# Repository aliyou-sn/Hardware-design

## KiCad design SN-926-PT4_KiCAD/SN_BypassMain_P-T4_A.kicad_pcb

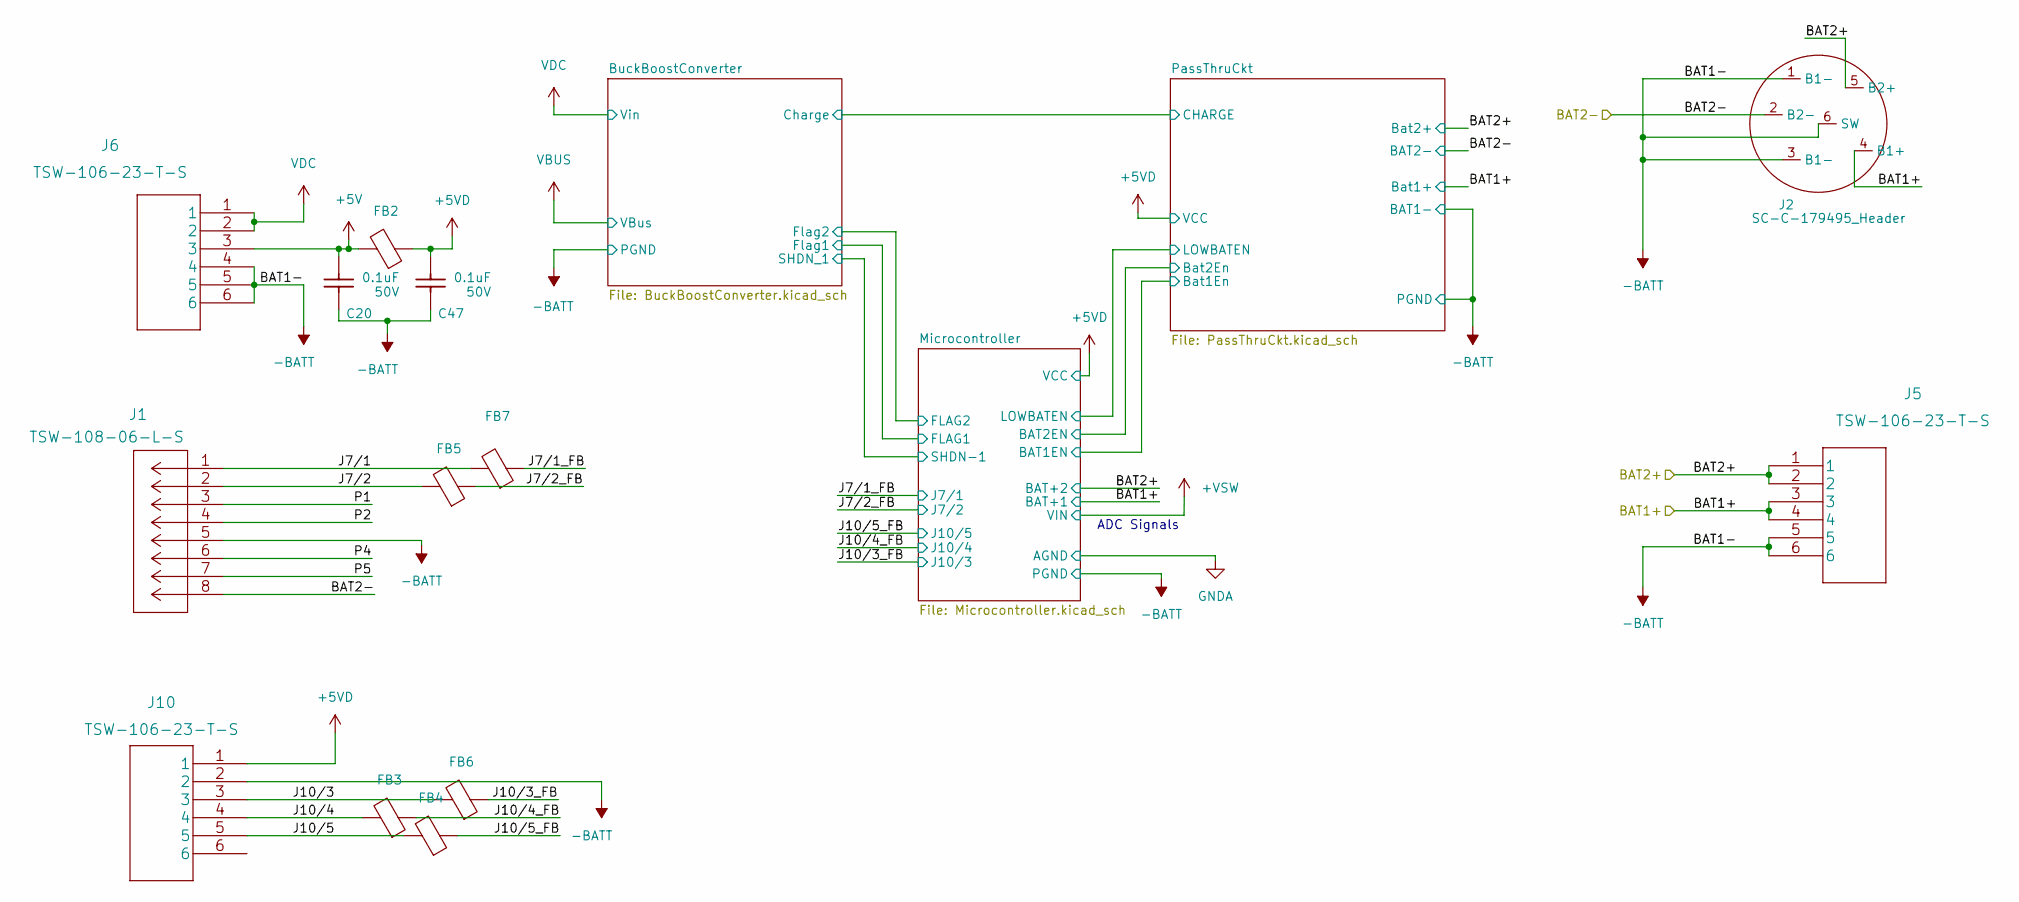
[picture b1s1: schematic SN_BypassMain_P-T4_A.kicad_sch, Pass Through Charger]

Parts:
C20, C47: 0.1uF; C_0603_1608Metric; VOLTAGE 50V; TOLERANCE +/-5%; MANUFACTURER PARTNO 2 12062C104JAT2A
FB2, FB3, FB4, FB5, FB6, FB7: BLM21AG121BH1D; L_0805_2012Metric
J1: TSW-108-06-L-S
J2: SC-C-179495_Header; SC-C-179495_HEADER
J5, J6, J10: TSW-106-23-T-S

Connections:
+5V: C20.2, FB2.2, J6.3
+5VD: C47.2, FB2.1, J10.1; also elsewhere on the board
-BATT: C20.1, C47.1, J1.5, J2.1 (B1-), J2.3 (B1-), J2.6 (SW), J5.5, J5.6, J6.4, J6.5, J6.6, J10.2; also elsewhere on the board
/BAT1+: J2.4 (B1+), J5.3, J5.4; also elsewhere on the board
/BAT2+: J2.5 (B2+), J5.1, J5.2; also elsewhere on the board
/BAT2-: J1.8, J2.2 (B2-); also elsewhere on the board
/J7/1: FB7.2, J1.1
/J7/1_FB: FB7.1; also elsewhere on the board
/J7/2: FB5.2, J1.2
/J7/2_FB: FB5.1; also elsewhere on the board
/J10/3: FB6.2, J10.3
/J10/3_FB: FB6.1; also elsewhere on the board
/J10/4: FB3.2, J10.4
/J10/4_FB: FB3.1; also elsewhere on the board
/J10/5: FB4.2, J10.5
/J10/5_FB: FB4.1; also elsewhere on the board
/P1: J1.3
/P2: J1.4
/P4: J1.6
/P5: J1.7
VDC: J6.1, J6.2; also elsewhere on the board

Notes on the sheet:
ADC Signals

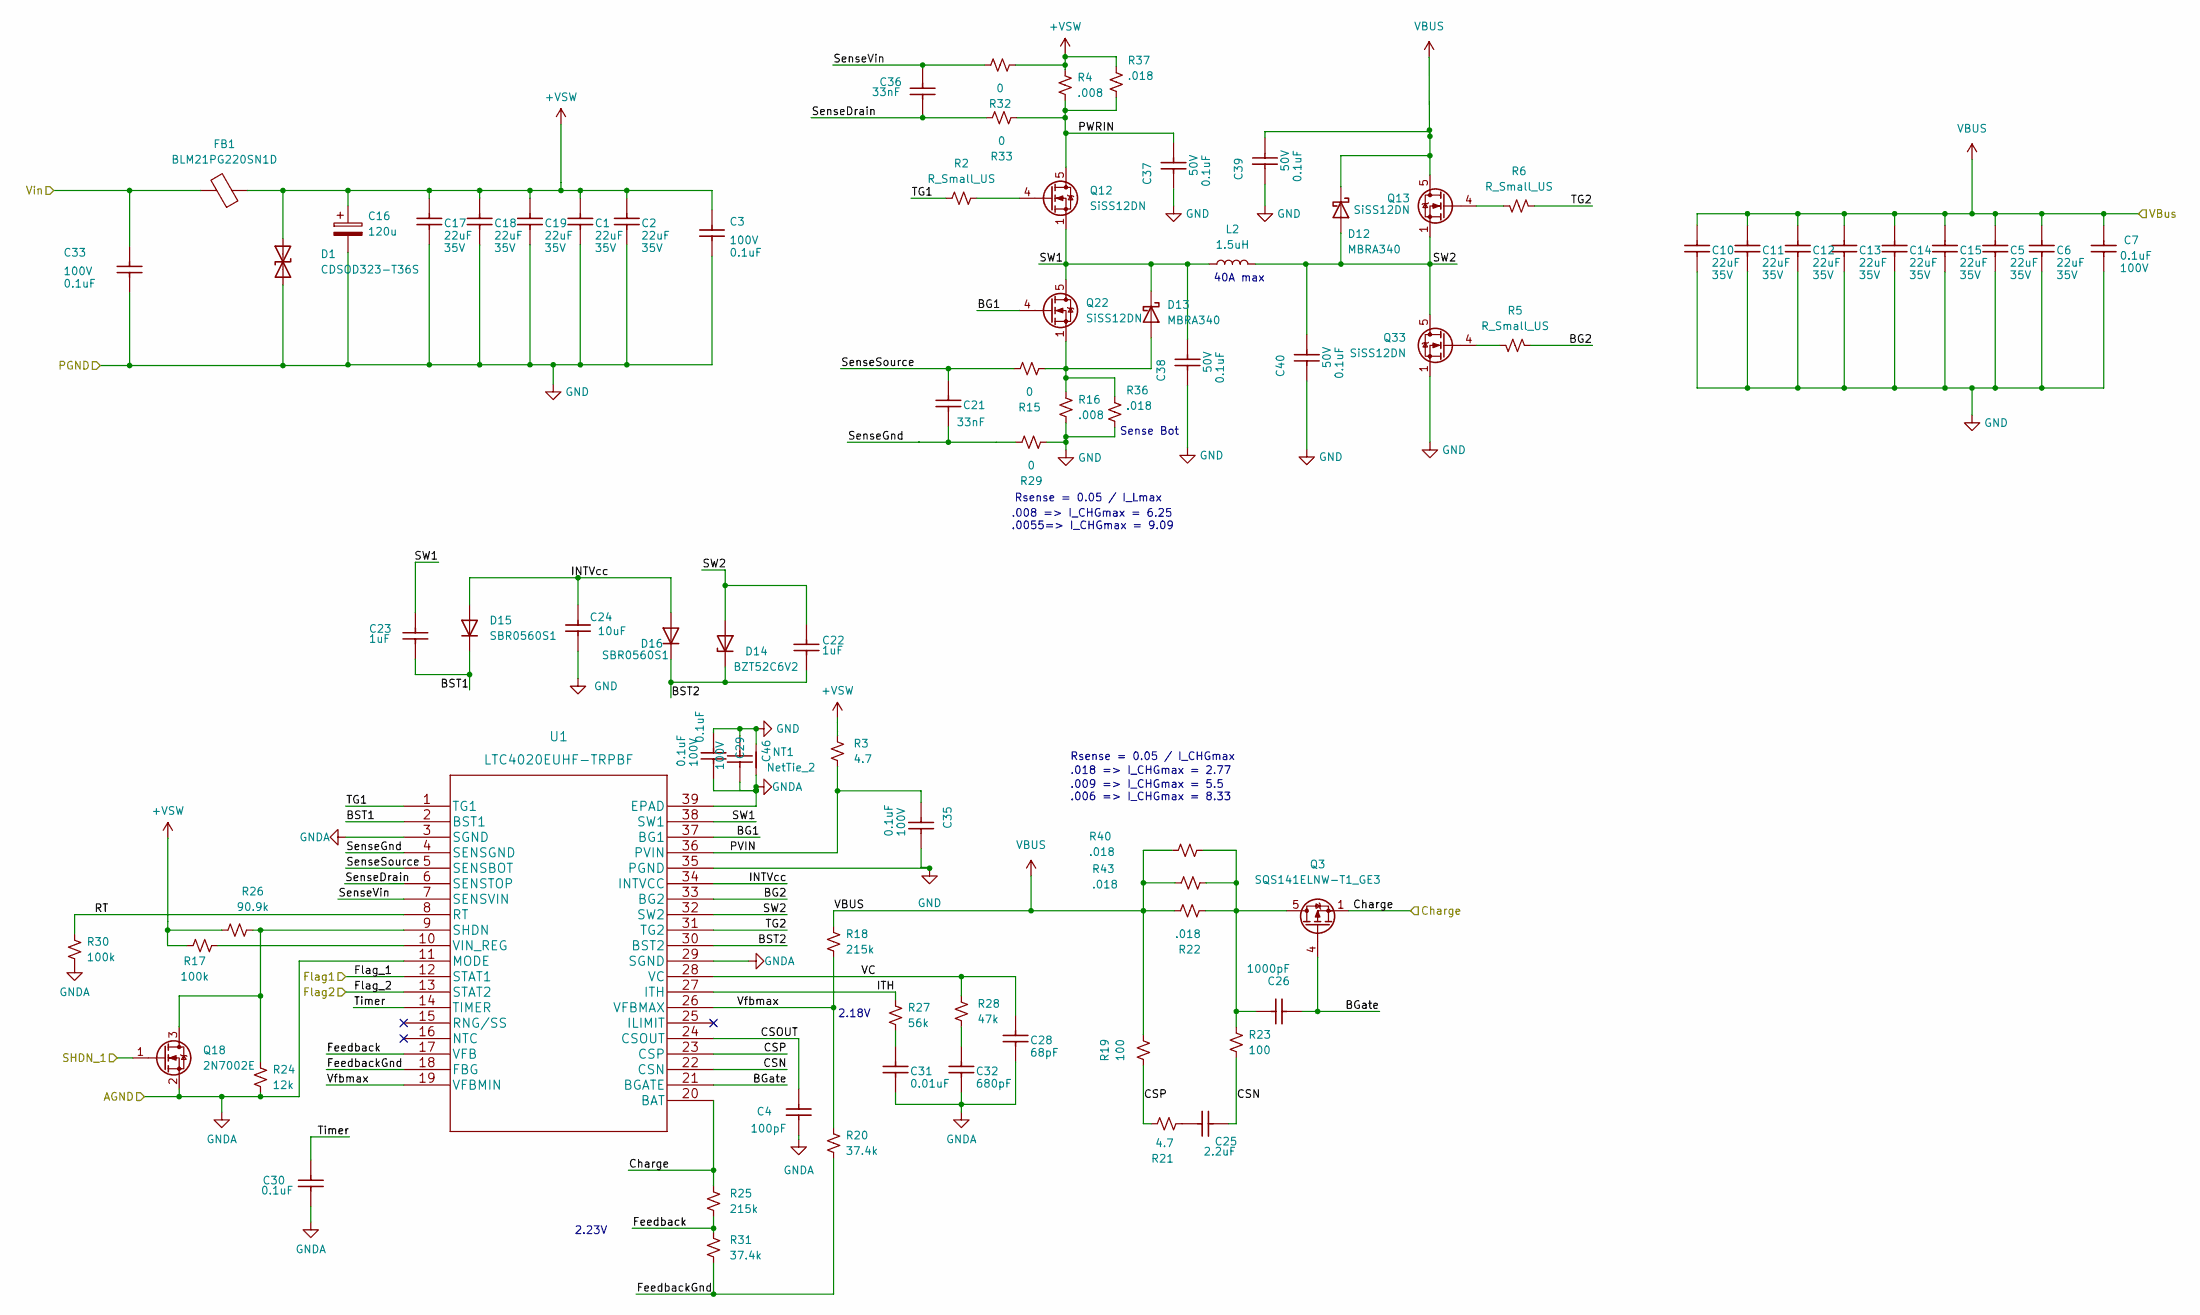
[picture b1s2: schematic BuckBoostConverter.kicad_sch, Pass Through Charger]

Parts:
C1, C2, C5, C6, C10, C11, C12, C13, C14, C15, C17, C18, C19: 22uF; C_1206_3216Metric; VOLTAGE 35V; TOLERANCE 20%; MANUFACTURER PARTNO C3216JB1V226M160AC
C3, C7, C29, C33, C35, C46: 0.1uF; C_0603_1608Metric; VOLTAGE 100V; TOLERANCE +/-5%; MANUFACTURER PARTNO 2 12062C104JAT2A
C4: 100pF; C_0402_1005Metric
C16: 120u; CP_Elec_10x10
C21, C36: 33nF; C_0402_1005Metric
C22, C23: 1uF; C_0603_1608Metric
C24: 10uF; C_1206_3216Metric
C25: 2.2uF; C_0402_1005Metric
C26: 1000pF; C_0402_1005Metric
C28: 68pF; C_0603_1608Metric
C30: 2.2uF; R_0402_1005Metric
C31: 0.01uF; C_0603_1608Metric
C32: 680pF; C_0603_1608Metric
C37, C38, C39, C40: 0.1uF; C_0603_1608Metric; VOLTAGE 50V; TOLERANCE +/-5%; MANUFACTURER PARTNO 2 12062C104JAT2A
D1: CDSOD323-T36S; D_SOD-323
D12, D13: MBRA340; D_SMA
D14: BZT52C6V2; D_SOD-123F
D15, D16: SBR0560S1; D_SOD-123
FB1: BLM21PG220SN1D; L_0805_2012Metric
L2: 1.5uH; XAL1010-152MEB
NT1: NetTie_2; NetTie-2_SMD_Pad0.5mm
Q3: SQS141ELNW-T1_GE3; Vishay_PowerPAK_1212-8_Single
Q12, Q13, Q22, Q33: SiSS12DN; Vishay_PowerPAK_1212-8_Single
Q18: 2N7002E; SOT-23
R2, R5, R6: R_Small_US; R_0402_1005Metric
R3: 4.7; R_0603_1608Metric
R4: .008
R15, R29, R32, R33: 0; C_0402_1005Metric
R16: .008; R_2512_6332Metric
R17, R30: 100k; R_0402_1005Metric
R18, R25: 215k; R_0402_1005Metric
R19, R23: 100; C_0402_1005Metric
R20, R31: 37.4k; R_0402_1005Metric
R21: 4.7; R_0402_1005Metric
R22, R36, R37, R40, R43: .018; R_2512_6332Metric
R24: 12k; R_0402_1005Metric
R26: 90.9k; R_0402_1005Metric
R27: 56k; R_0603_1608Metric
R28: 47k; R_0603_1608Metric
U1: LTC4020EUHF-TRPBF

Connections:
+VSW: C1.1, C2.1, C3.1, C16.1, C17.1, C18.1, C19.1, D1.1 (A1), FB1.1, R3.2, R4.2, R17.1, R26.1, R32.2, R37.2; also elsewhere on the board
-BATT: C1.2, C2.2, C3.2, C5.2, C6.2, C7.2, C10.2, C11.2, C12.2, C13.2, C14.2, C15.2, C16.2, C17.2, C18.2, C19.2, C24.1, C29.1, C33.2, C35.2, C37.1, C38.1, C39.1, C40.1, C46.1, D1.2 (A2), NT1.1, Q33.1 (S), Q33.2 (S), Q33.3 (S), R16.2, R29.2, R36.1, U1.35 (PGND); also elsewhere on the board
/BuckBoostConverter/BG1: Q22.4 (G), U1.37 (BG1)
/BuckBoostConverter/BG2: R5.1, U1.33 (BG2)
/BuckBoostConverter/BGate: C26.2, Q3.4 (G), U1.21 (BGATE); also elsewhere on the board
/BuckBoostConverter/BST1: C23.1, D15.1 (K), U1.2 (BST1)
/BuckBoostConverter/BST2: C22.1, D14.1 (K), D16.1 (K), U1.30 (BST2)
/BuckBoostConverter/CSN: C25.2, R23.1, U1.22 (CSN)
/BuckBoostConverter/CSOUT: C4.1, U1.24 (CSOUT)
/BuckBoostConverter/CSP: R19.2, R21.1, U1.23 (CSP)
/BuckBoostConverter/Charge: Q3.1 (S), Q3.2 (S), Q3.3 (S), R25.2, U1.20 (BAT); also elsewhere on the board
/BuckBoostConverter/Feedback: R25.1, R31.2, U1.17 (VFB)
/BuckBoostConverter/FeedbackGnd: R20.1, R31.1, U1.18 (FBG)
/BuckBoostConverter/Flag_1: U1.12 (STAT1); also elsewhere on the board
/BuckBoostConverter/Flag_2: U1.13 (STAT2); also elsewhere on the board
/BuckBoostConverter/INTVcc: C24.2, D15.2 (A), D16.2 (A), U1.34 (INTVCC)
/BuckBoostConverter/ITH: R27.2, U1.27 (ITH)
/BuckBoostConverter/PVIN: C35.1, R3.1, U1.36 (PVIN)
/BuckBoostConverter/PWRIN: C37.2, Q12.5 (D), R4.1, R33.2, R37.1
/BuckBoostConverter/RT: R30.1, U1.8 (RT)
/BuckBoostConverter/SW1: C23.2, C38.2, D13.1 (K), L2.1, Q12.1 (S), Q12.2 (S), Q12.3 (S), Q22.5 (D), U1.38 (SW1)
/BuckBoostConverter/SW2: C22.2, C40.2, D12.2 (A), D14.2 (A), L2.2, Q13.1 (S), Q13.2 (S), Q13.3 (S), Q33.5 (D), U1.32 (SW2)
/BuckBoostConverter/SenseDrain: C36.1, R33.1, U1.6 (SENSTOP)
/BuckBoostConverter/SenseGnd: C21.2, R29.1, U1.4 (SENSGND)
/BuckBoostConverter/SenseSource: C21.1, R15.1, U1.5 (SENSBOT)
/BuckBoostConverter/SenseVin: C36.2, R32.1, U1.7 (SENSVIN)
/BuckBoostConverter/TG1: R2.1, U1.1 (TG1)
/BuckBoostConverter/TG2: R6.1, U1.31 (TG2)
/BuckBoostConverter/Timer: C30.1, U1.14 (TIMER)
/BuckBoostConverter/VC: C28.1, R28.2, U1.28 (VC)
/BuckBoostConverter/Vfbmax: R18.1, R20.2, U1.19 (VFBMIN), U1.26 (VFBMAX)
/Microcontroller/SHDN-1: Q18.1 (G); also elsewhere on the board
GNDA: C4.2, C28.2, C29.2, C30.2, C31.2, C32.2, C46.2, NT1.2, Q18.2 (S), R24.2, R30.2, U1.3 (SGND), U1.11 (MODE), U1.29 (SGND), U1.39 (EPAD); also elsewhere on the board
unnamed: C25.1, R21.2
unnamed 59: C26.1, Q3.5 (D), Q3.6 (D), Q3.7 (D), Q3.8 (D), Q3.9 (D), R22.1, R23.2, R40.2, R43.2; also elsewhere on the board
unnamed: C31.1, R27.1
unnamed: C32.1, R28.1
unnamed: D13.2 (A), Q22.1 (S), Q22.2 (S), Q22.3 (S), R15.2, R16.1, R36.2
unnamed: Q12.4 (G), R2.2
unnamed: Q13.4 (G), R6.2
unnamed: Q18.3 (D), R24.1, R26.2, U1.9 (SHDN)
unnamed: Q33.4 (G), R5.2
unnamed: R17.2, U1.10 (VIN_REG)
VBUS: C5.1, C6.1, C7.1, C10.1, C11.1, C12.1, C13.1, C14.1, C15.1, C39.2, D12.1 (K), Q13.5 (D), R18.2, R19.1, R22.2, R40.1, R43.1
VDC: C33.1, FB1.2; also elsewhere on the board

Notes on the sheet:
.018 => I_CHGmax = 2.77
2.18V
Rsense = 0.05 / I_Lmax
.008 => I_CHGmax = 6.25 .0055=> I_CHGmax = 9.09
Sense Bot
.006 => I_CHGmax = 8.33
Rsense = 0.05 / I_CHGmax
.009 => I_CHGmax = 5.5
2.23V
40A max

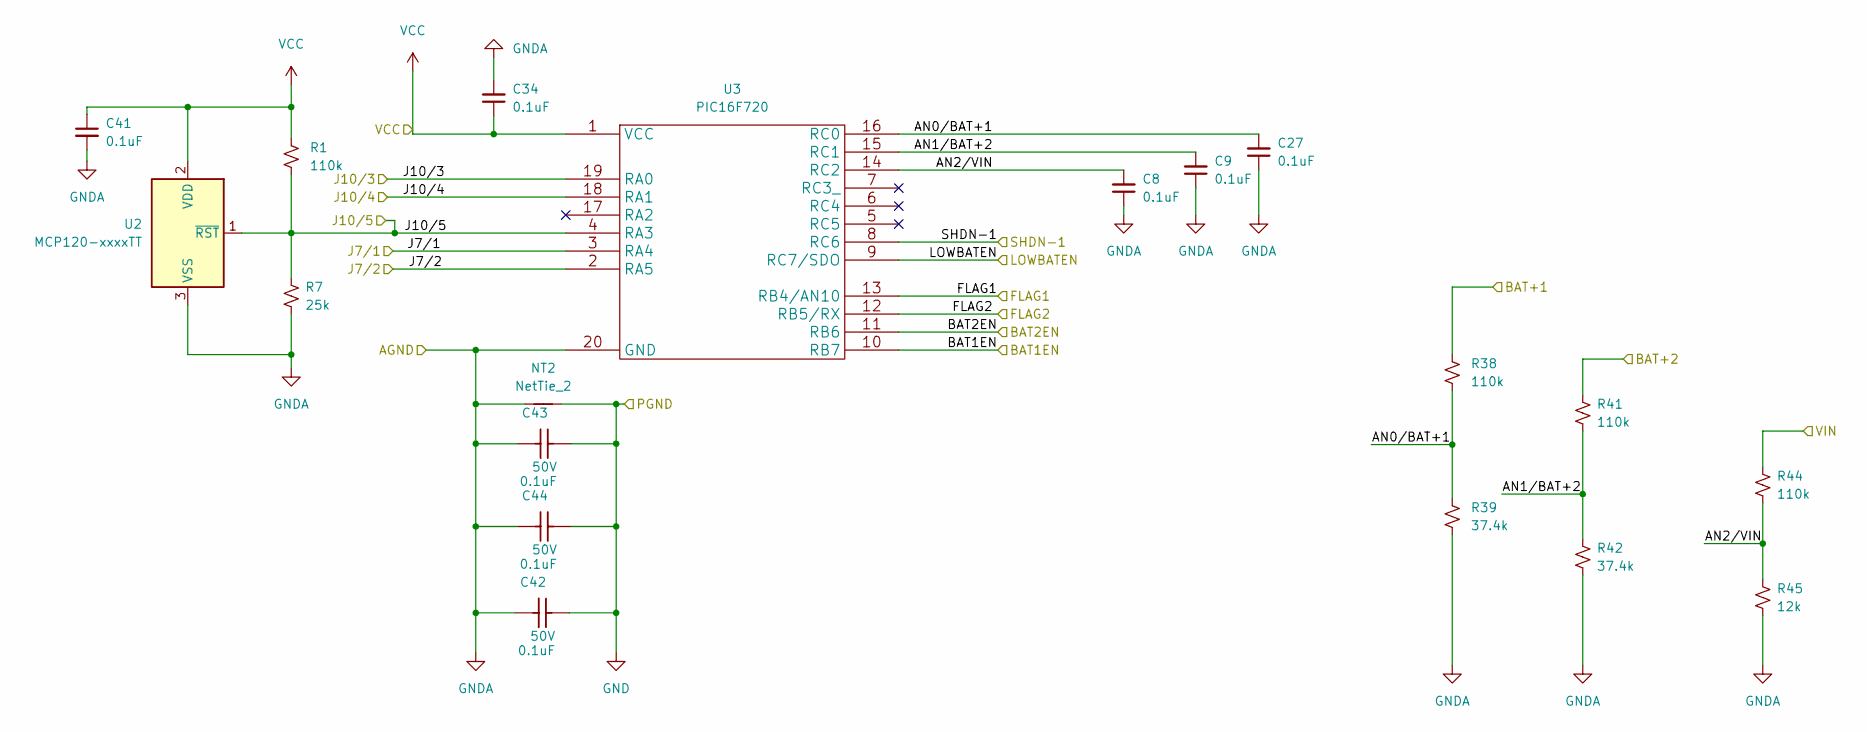
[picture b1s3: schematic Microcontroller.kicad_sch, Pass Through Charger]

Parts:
C8, C9, C27, C34: 0.1uF; C_0402_1005Metric
C41: 0.1uF; C_0603_1608Metric
C42, C43, C44: 0.1uF; C_0603_1608Metric; VOLTAGE 50V; TOLERANCE +/-5%; MANUFACTURER PARTNO 2 12062C104JAT2A
NT2: NetTie_2
R1, R38, R41, R44: 110k; R_0402_1005Metric
R7: 25k; R_0402_1005Metric
R39, R42: 37.4k; R_0402_1005Metric
R45: 12k; R_0402_1005Metric
U2: MCP120-xxxxTT; SOT-23
U3: PIC16F720; SSOP-20_5.3x7.2mm_P0.65mm

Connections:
+5VD: C34.1, C41.1, R1.1, U2.2 (VDD), U3.1 (VCC); also elsewhere on the board
+VSW: R44.1; also elsewhere on the board
-BATT: C42.2, C43.2, C44.2, NT2.2; also elsewhere on the board
/BAT1+: R38.1; also elsewhere on the board
/BAT2+: R41.1; also elsewhere on the board
/BuckBoostConverter/Flag_1: U3.13 (RB4/AN10); also elsewhere on the board
/BuckBoostConverter/Flag_2: U3.12 (RB5/RX); also elsewhere on the board
/J7/1_FB: U3.3 (RA4); also elsewhere on the board
/J7/2_FB: U3.2 (RA5); also elsewhere on the board
/J10/3_FB: U3.19 (RA0); also elsewhere on the board
/J10/4_FB: U3.18 (RA1); also elsewhere on the board
/J10/5_FB: R1.2, R7.1, U2.1 (~RST), U3.4 (RA3); also elsewhere on the board
/Microcontroller/AN0/BAT+1: C27.2, R38.2, R39.1, U3.16 (RC0)
/Microcontroller/AN1/BAT+2: C9.2, R41.2, R42.1, U3.15 (RC1)
/Microcontroller/AN2/VIN: C8.2, R44.2, R45.1, U3.14 (RC2)
/Microcontroller/BAT1EN: U3.10 (RB7); also elsewhere on the board
/Microcontroller/BAT2EN: U3.11 (RB6); also elsewhere on the board
/Microcontroller/LOWBATEN: U3.9 (RC7/SDO); also elsewhere on the board
/Microcontroller/SHDN-1: U3.8 (RC6); also elsewhere on the board
GNDA: C8.1, C9.1, C27.1, C34.2, C41.2, C42.1, C43.1, C44.1, NT2.1, R7.2, R39.2, R42.2, R45.2, U2.3 (VSS), U3.20 (GND); also elsewhere on the board

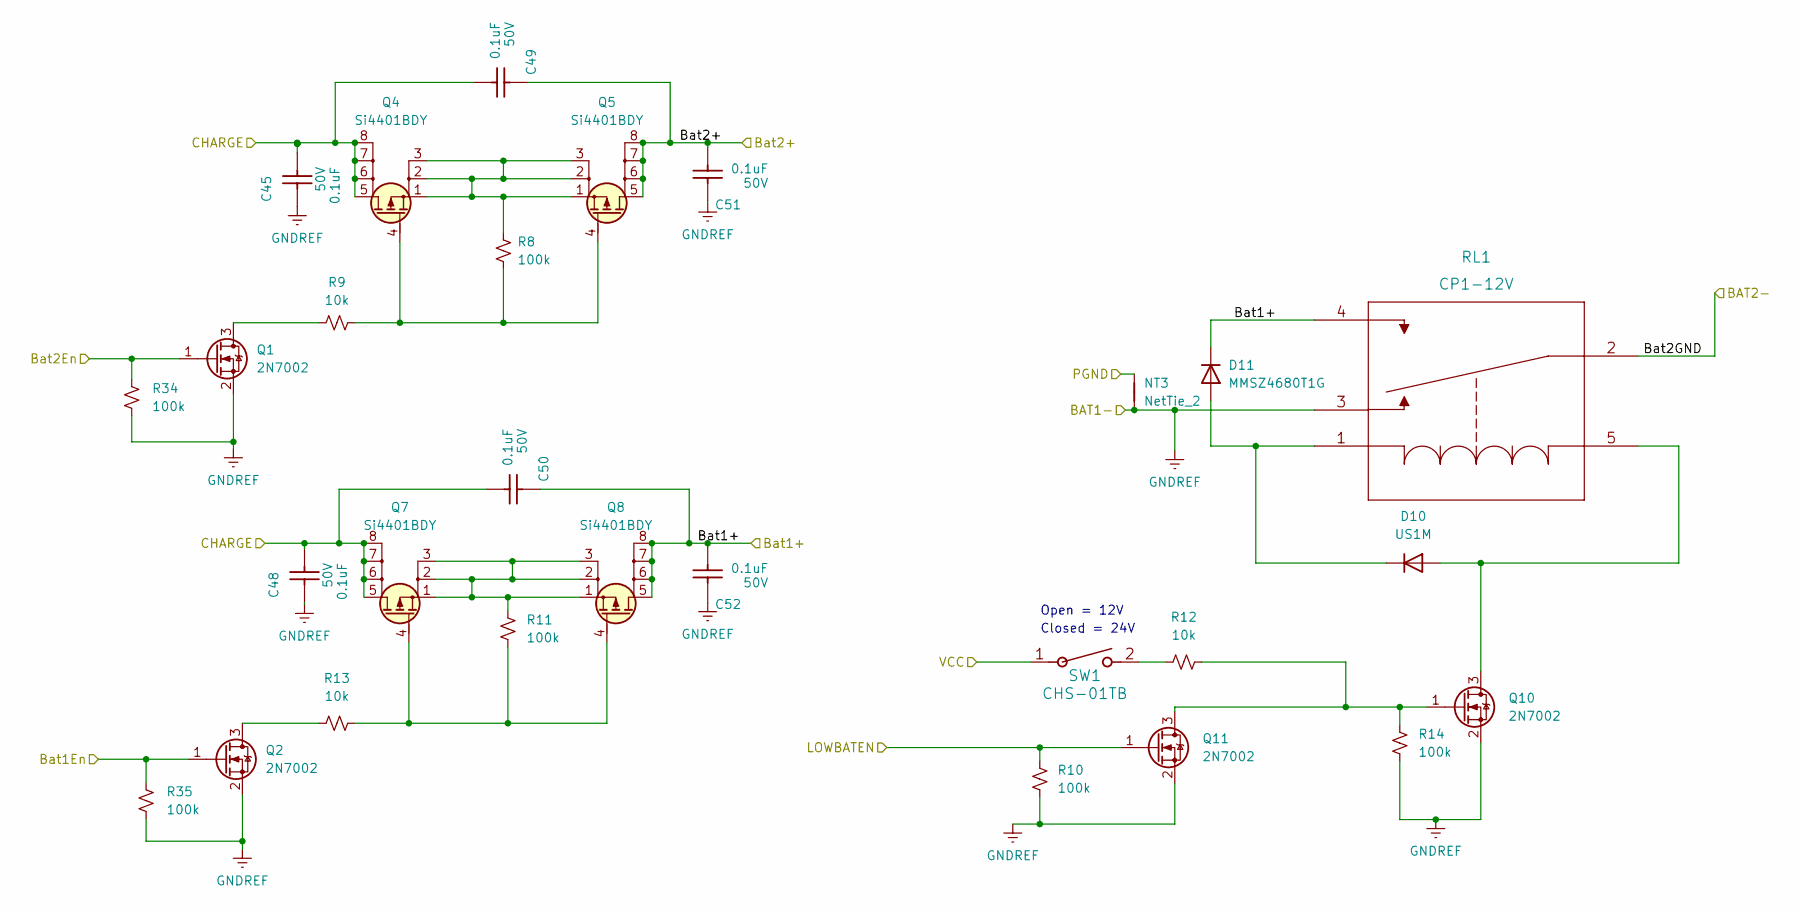
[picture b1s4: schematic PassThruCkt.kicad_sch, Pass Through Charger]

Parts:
C45, C48, C51, C52: 0.1uF; C_0603_1608Metric; VOLTAGE 50V; TOLERANCE +/-5%; MANUFACTURER PARTNO 2 12062C104JAT2A
C49, C50: 0.1uF; C_1206_3216Metric; VOLTAGE 50V; TOLERANCE +/-5%; MANUFACTURER PARTNO 2 12062C104JAT2A
D10: US1M; D_SMA
D11: MMSZ4680T1G; D_SOD-123
NT3: NetTie_2
Q1, Q2, Q10, Q11: 2N7002; SOT-23
Q4, Q5, Q7, Q8: Si4401BDY; SO-8_3.9x4.9mm_P1.27mm
R8, R10, R11, R14, R34, R35: 100k; R_0402_1005Metric
R9, R12, R13: 10k; R_0402_1005Metric
RL1: CP1-12V; CP112V
SW1: CHS-01TB

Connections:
+5VD: SW1.1; also elsewhere on the board
-BATT: C45.1, C48.1, C51.1, C52.1, NT3.1, Q1.2 (S), Q2.2 (S), Q10.2 (S), Q11.2 (S), R10.2, R14.1, R34.2, R35.2, RL1.3; also elsewhere on the board
/BAT1+: C50.1, C52.2, D11.1 (K), Q8.5 (D), Q8.6 (D), Q8.7 (D), Q8.8 (D), RL1.4; also elsewhere on the board
/BAT2+: C49.1, C51.2, Q5.5 (D), Q5.6 (D), Q5.7 (D), Q5.8 (D); also elsewhere on the board
/BAT2-: RL1.2; also elsewhere on the board
/BuckBoostConverter/Charge: C45.2, C48.2, C49.2, C50.2, Q4.5 (D), Q4.6 (D), Q4.7 (D), Q4.8 (D), Q7.5 (D), Q7.6 (D), Q7.7 (D), Q7.8 (D); also elsewhere on the board
/Microcontroller/BAT1EN: Q2.1 (G), R35.1; also elsewhere on the board
/Microcontroller/BAT2EN: Q1.1 (G), R34.1; also elsewhere on the board
/Microcontroller/LOWBATEN: Q11.1 (G), R10.1; also elsewhere on the board
unnamed: D10.1 (K), D11.2 (A), RL1.1
unnamed: D10.2 (A), Q10.3 (D), RL1.5
unnamed: Q1.3 (D), R9.1
unnamed: Q2.3 (D), R13.1
unnamed: Q4.1 (S), Q4.2 (S), Q4.3 (S), Q5.1 (S), Q5.2 (S), Q5.3 (S), R8.1
unnamed: Q4.4 (G), Q5.4 (G), R8.2, R9.2
unnamed: Q7.1 (S), Q7.2 (S), Q7.3 (S), Q8.1 (S), Q8.2 (S), Q8.3 (S), R11.1
unnamed: Q7.4 (G), Q8.4 (G), R11.2, R13.2
unnamed: Q10.1 (G), Q11.3 (D), R12.2, R14.2
unnamed: R12.1, SW1.2

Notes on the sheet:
Open = 12V
Closed = 24V

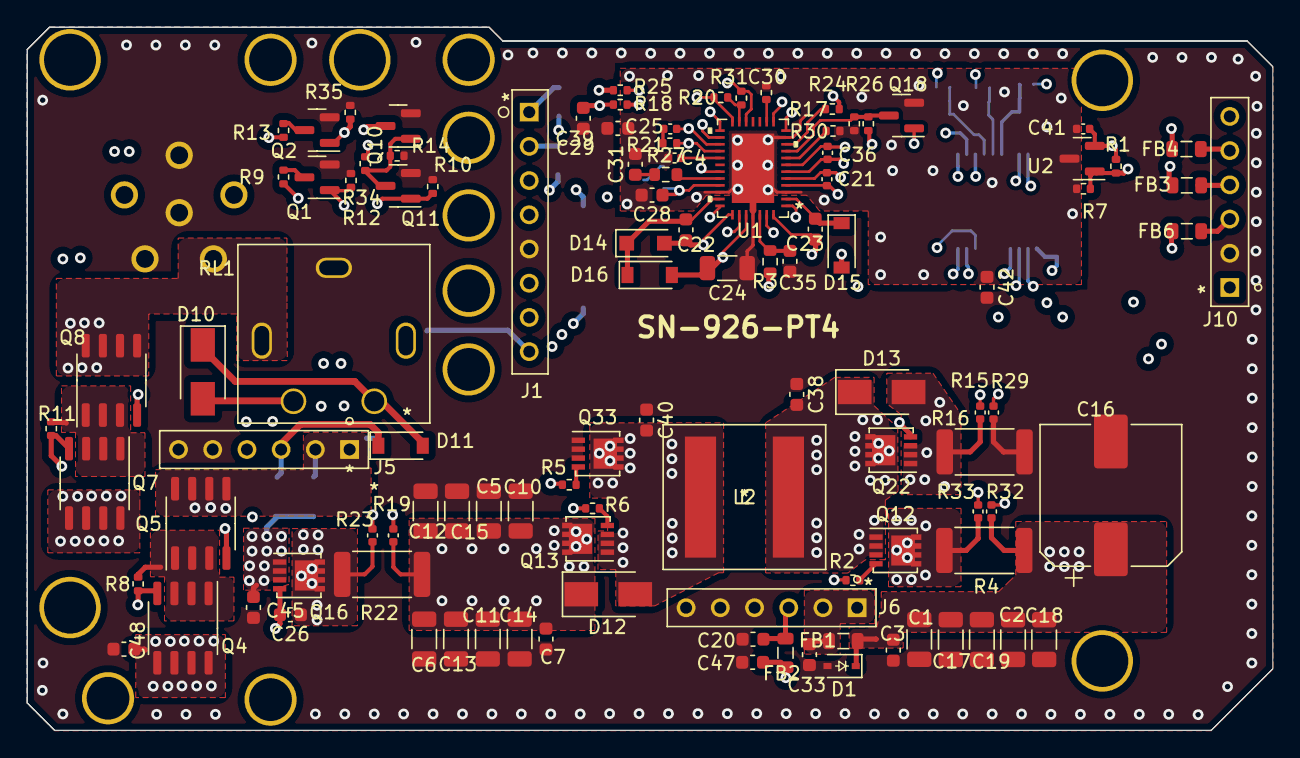
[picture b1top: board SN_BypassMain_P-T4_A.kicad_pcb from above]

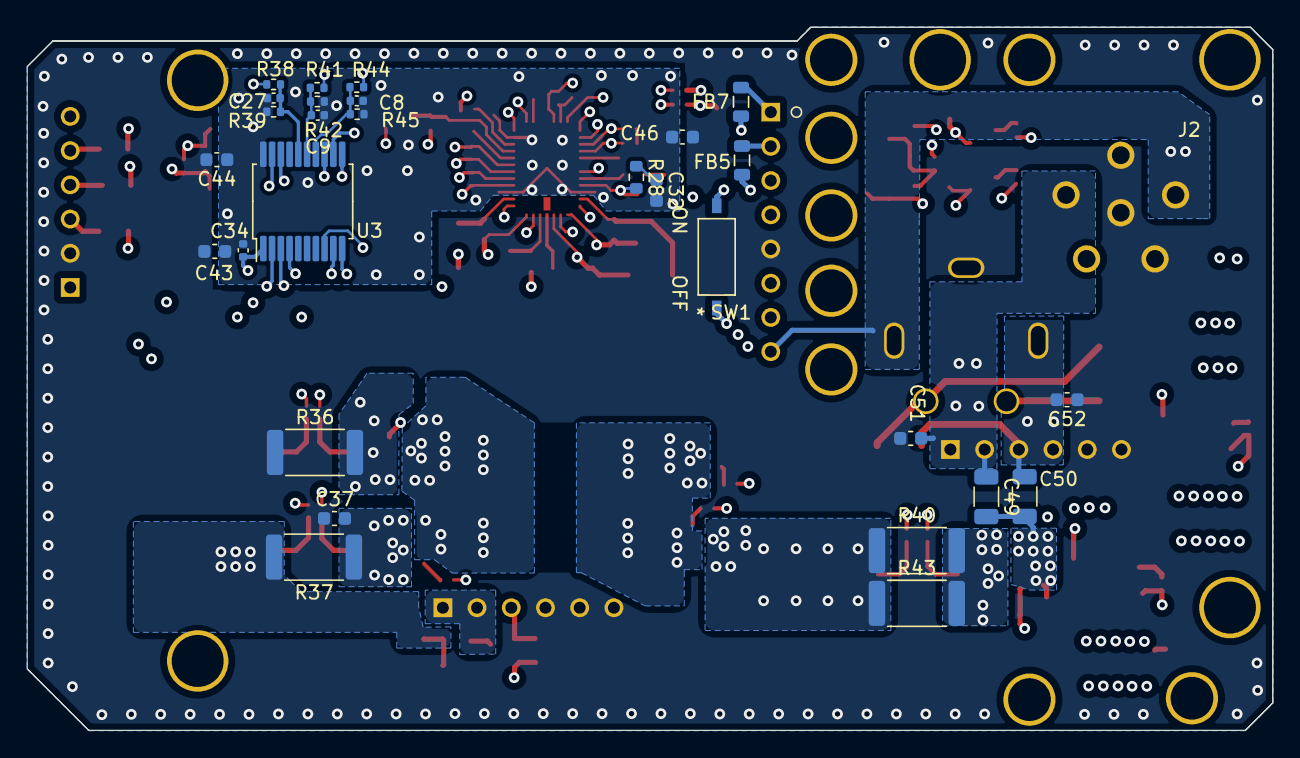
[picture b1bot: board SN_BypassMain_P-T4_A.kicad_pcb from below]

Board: 4 copper layers, 92.5 x 52.2 mm, 138 parts (29 on the bottom side), 76 nets.

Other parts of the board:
Q16: SQS141ELNW-T1_GE3; Vishay_PowerPAK_1212-8_Single

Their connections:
/BuckBoostConverter/BGate: Q16.4 (G); also elsewhere on the board
/BuckBoostConverter/Charge: Q16.1 (S), Q16.2 (S), Q16.3 (S); also elsewhere on the board
unnamed 59: Q16.5 (D); also elsewhere on the board

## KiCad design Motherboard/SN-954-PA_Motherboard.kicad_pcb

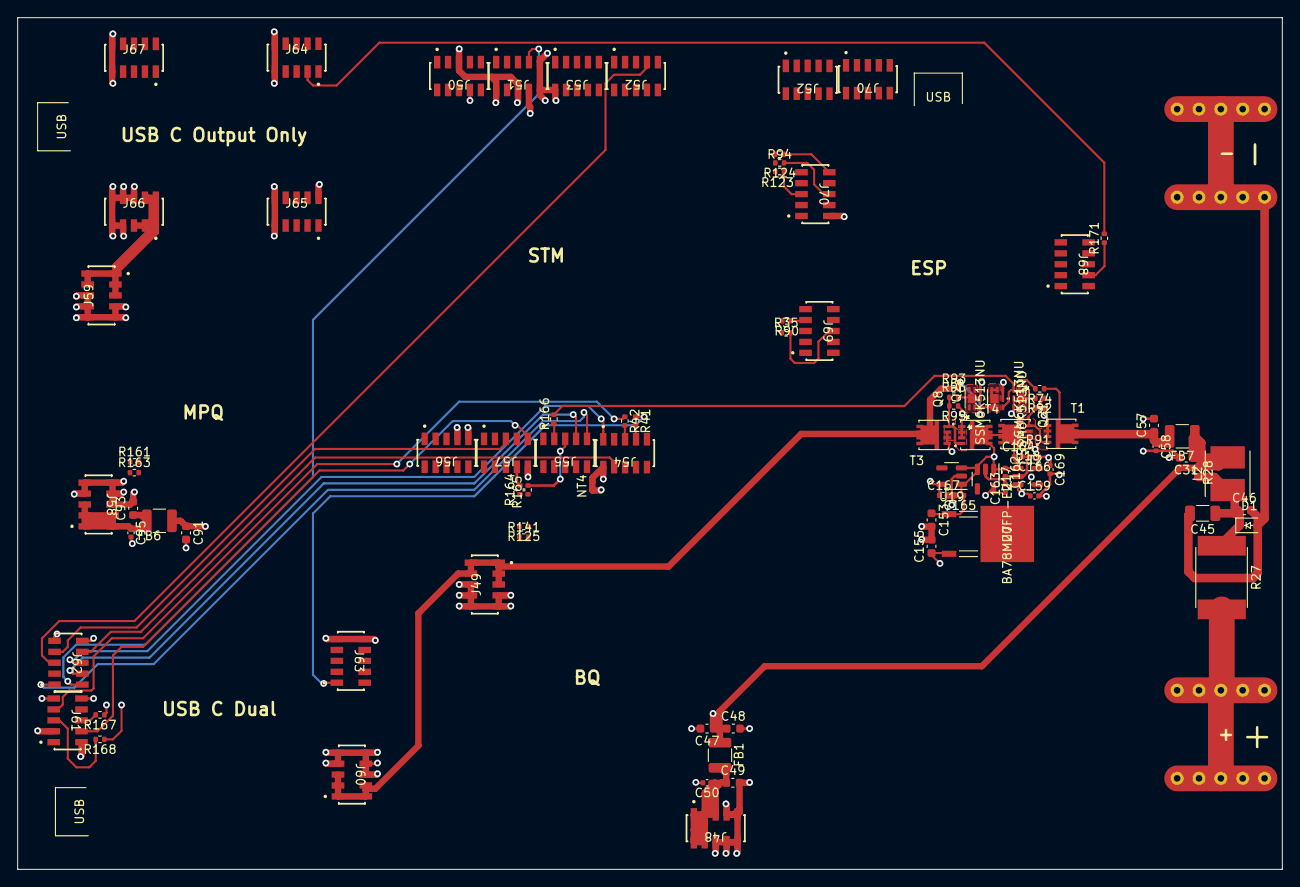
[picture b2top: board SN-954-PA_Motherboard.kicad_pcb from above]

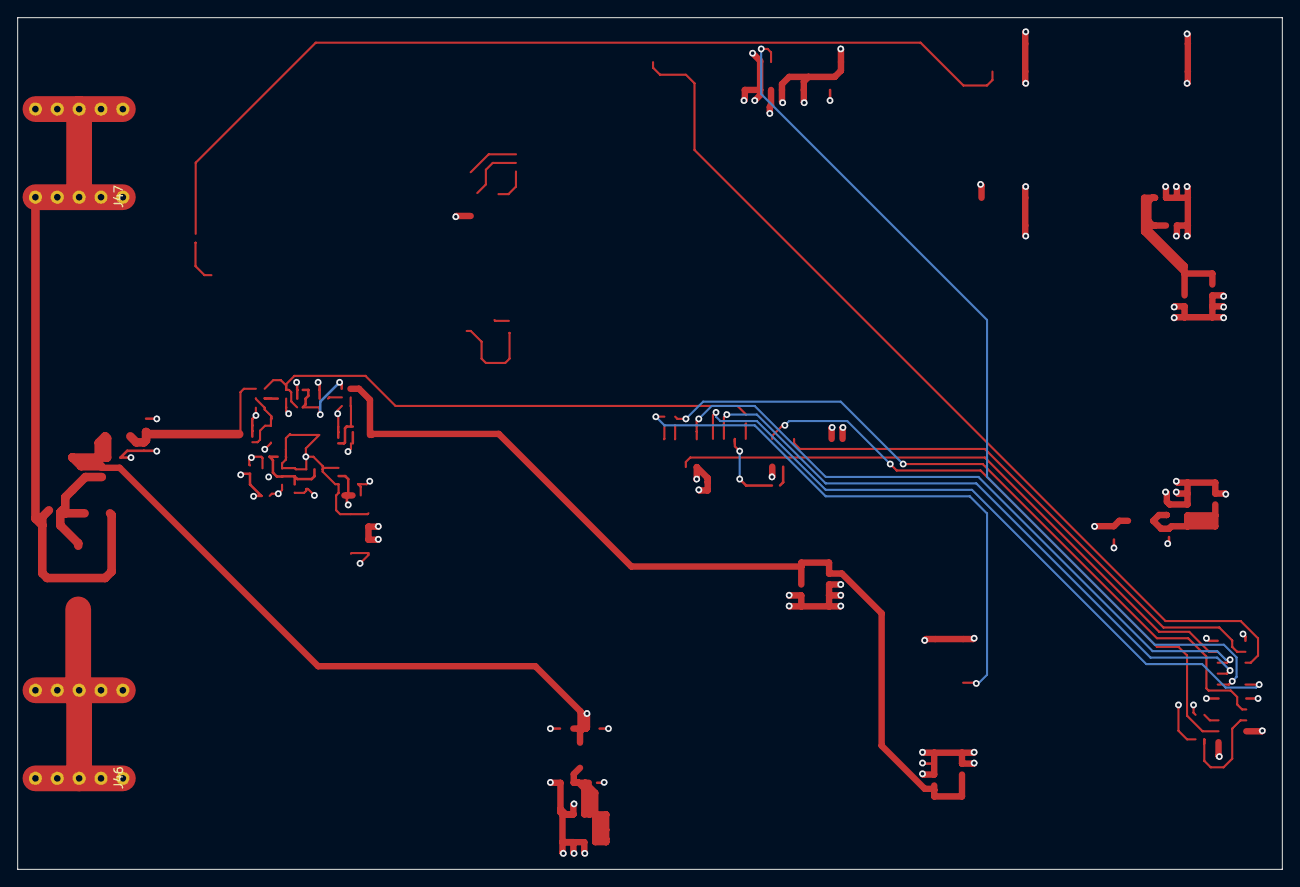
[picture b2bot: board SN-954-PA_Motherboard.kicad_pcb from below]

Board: 4 copper layers, 147.0 x 99.0 mm, 91 parts (2 on the bottom side), 48 nets.

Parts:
C31, C46, C48, C49, C57, C91, C93: 510pF; C_0603_1608Metric
C45: 10uF; C_1206_3216Metric
C47, C153, C155: 2.2uF; C_0603_1608Metric
C50, C58, C95, C159, C162, C163, C164, C165, C166, C167, C169: 0.1uF; C_0402_1005Metric
D1: CDSOD323-T36S; D_SOD-323
FB1, FB6, FB7: FerriteBead; R_1210_3225Metric
J46, J47: Conn_01x01_Female; 7461106_WuerthTB
J48, J49, J50, J51, J52, J52#2, J53, J54, J55, J56, J57, J58, J59, J60, J61, J62, J63, J64, J65, J66, J67, J68, J69, J70, J70#2: Conn_01x10_Female; CLP-105-02-L-D
L2: 1.5uH; L_TDK_VLS5030EX-D
NT4: Mechanical-NetTie_2; NetTie-2_SMD_Pad0.5mm
Q8, Q21, Q22: SSM6K513NU; SSM6K513NU_LF
R27: 0ZCF0500FF2A; Fuse_BelFuse_7.98x5.44mm
R28: 2.2k; R_0402_1005Metric
R35, R41, R42, R90, R94, R123, R124, R125, R141, R161, R163, R164, R165, R166, R167, R168: 0; R_0402_1005Metric
R74, R92, R96: 20k; R_0402_1005Metric
R91, R93, R95: 200k; R_0402_1005Metric
R171: 2k; R_0402_1005Metric
T1, T2, T3, T4: SQS414CENW-T1_GE3; SQS401EN-T1_BE3
U7: BA78M20FP-E2
U17, U19: SPX3819M5-L-5-0; SOT-23-5
U18: AP2204K-3.3; SOT-23-5

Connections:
+3.3V: C166.1, C169.1, J50.5, J51.2, J51.6, J56.7, J61.2, J70.2, U18.5 (VOUT)
+5V: C163.1, C167.1, J51.8, J61.3, J65.2, U17.5 (OUT), U19.5 (OUT)
+BATT: C49.1, C50.1, FB1.2, J48.1, J48.2, J48.3, J48.4, J48.5
+VDC: C93.1, C95.1, FB6.2, J58.1, J58.2, J58.3, J58.4, J58.5
-BATT: C45.2, C46.2, D1.2 (A2), J47.1
/20V: C155.1, U7.3 (OUTPUT)
/BoardPowerSupply/VBoardPower: C57.1, C58.1, FB7.2, R74.1, T1.5 (D)
/BoardPowerSupply/VDC: C153.1, C159.1, C162.1, C164.1, C165.1, T2.5 (D), T4.5 (D), U7.1 (INPUT), U17.1 (IN), U17.3 (EN), U18.1 (VIN), U18.3 (EN), U19.1 (IN), U19.3 (EN)
/BoardPowerSupply//DRP: Q8.1 (D), Q8.2 (D), Q8.5 (D), Q8.6 (D), Q22.3 (G), R93.2
/DRP: Q8.3 (G), Q21.3 (G), R74.2, R166.1
/FB_0: J64.3, R171.2
/ISense: J57.5, J62.7
/Input Filter/BAT+: J46.1, R27.2
/Input Filter/VFilterMain: C31.1, C47.1, C48.1, C91.1, FB1.1, FB6.1, FB7.1, L2.2, R28.1
/Micro_Master/I39: J68.4, R171.1
/Micro_Master/IO4: J70.5, R123.1
/Micro_Master/IO15: J70.10, R94.2
/Micro_Master/IO16: J70.6, R124.1
/Micro_Master/IO21: J69.7, R90.1
/Micro_Master/IO22: J69.6, R35.2
/SCL: R35.1, R141.1, R163.1, R165.1, R168.1
/SDA: R90.2, R125.2, R161.2, R164.1, R167.1
/STUSB160x_1/AB_SIDE_1: J63.1, R41.1
/STUSB160x_1/ALERT_1: J61.7, R42.1
/STUSB160x_1/CS_1: J51.7, J62.2
/STUSB160x_1/MISO_1: J55.7, J62.4
/STUSB160x_1/MOSI_1: J55.9, J62.1
/STUSB160x_1/RESET_1: J57.9, J61.4
/STUSB160x_1/SCK_1: J54.1, J62.6
/STUSB160x_1/SCL: J61.5, R168.2
/STUSB160x_1/SDA: J61.6, R167.2
/STUSB160x_1/TX_EN_1: J52.7, J62.5
/USB C In-Out Interface/PA8: J55.3, R166.2
/USB C In-Out Interface/PB10: J55.5, R165.2
/USB C In-Out Interface/PB11: J57.8, R164.2
/USB C In-Out Interface/STLINK_USART_RX: J54.7, R41.2
/USB C In-Out Interface/STLINK_USART_TX: J54.5, R42.2
/VSense: J54.4, J62.8
GND: C31.2, C47.2, C48.2, C49.2, C50.2, C57.2, C58.2, C91.2, C93.2, C95.2, C153.2, C155.2, C159.2, C162.2, C163.2, C164.2, C165.2, C166.2, C167.2, C169.2, J48.6, J48.7, J48.8, J48.9, J48.10, J49.6, J49.7, J49.8, J49.9, J49.10, J50.8, J51.9, J51.10, J53.2, J54.2, J56.9, J57.10, J58.6, J58.7, J58.8, J58.9, J58.10, J59.6, J59.7, J59.8, J59.9, J59.10, J60.6, J60.7, J60.8, J60.9, J60.10, J61.9, J61.10, J62.9, J62.10, J63.9, J63.10, J64.9, J64.10, J65.9, J65.10, J66.6, J66.7, J66.8, J66.9, J66.10, J67.9, J67.10, NT4.1, NT4.2, Q8.4 (S), Q21.4 (S), Q22.4 (S), U17.2 (GND), U18.2 (GND), U19.2 (GND)
unnamed: C45.1, C46.1, D1.1 (A1), L2.1, R27.1, R28.2
unnamed: Q21.1 (D), Q21.2 (D), Q21.5 (D), Q21.6 (D), R92.2
unnamed: Q22.1 (D), Q22.2 (D), Q22.5 (D), Q22.6 (D), R96.2
unnamed: R91.1, T1.1 (S), T1.2 (S), T1.3 (S), T2.1 (S), T2.2 (S), T2.3 (S)
unnamed: R91.2, R92.1, T1.4 (G), T2.4 (G)
unnamed: R95.1, T3.1 (S), T3.2 (S), T3.3 (S), T4.1 (S), T4.2 (S), T4.3 (S)
unnamed: R95.2, R96.1, T3.4 (G), T4.4 (G)
VBUS: J49.1, J49.2, J49.3, J49.4, J49.5, J60.1, J60.2, J60.3, J60.4, J60.5, R93.1, T3.5 (D)
VS: J59.1, J59.2, J59.3, J59.4, J59.5, J66.1, J66.2, J66.3, J66.4, J66.5

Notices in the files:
parts and their libraries:
Copyright 2021 Accelerated Designs. All rights reserved.
